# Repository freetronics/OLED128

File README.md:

Kicad Schematic and PCB layout files for the Freetronics OLED128 module. Based around the SSD1351 OLED controller chip.

Designed by Angus Gratton and Marc Alexander.

Copyright (C) 2013 Freetronics Pty Ltd. Open Source Hardware, licensed under the TAPR Open Hardware License.

# Resources

[OLED128 Home Page](http://freetronics.com/oled128)

[OLED128 QuickStart Guide](http://freetronics.com/pages/oled128-quickstart-guide)

[FTOLED Arduino Library](https://github.com/freetronics/FTOLED)

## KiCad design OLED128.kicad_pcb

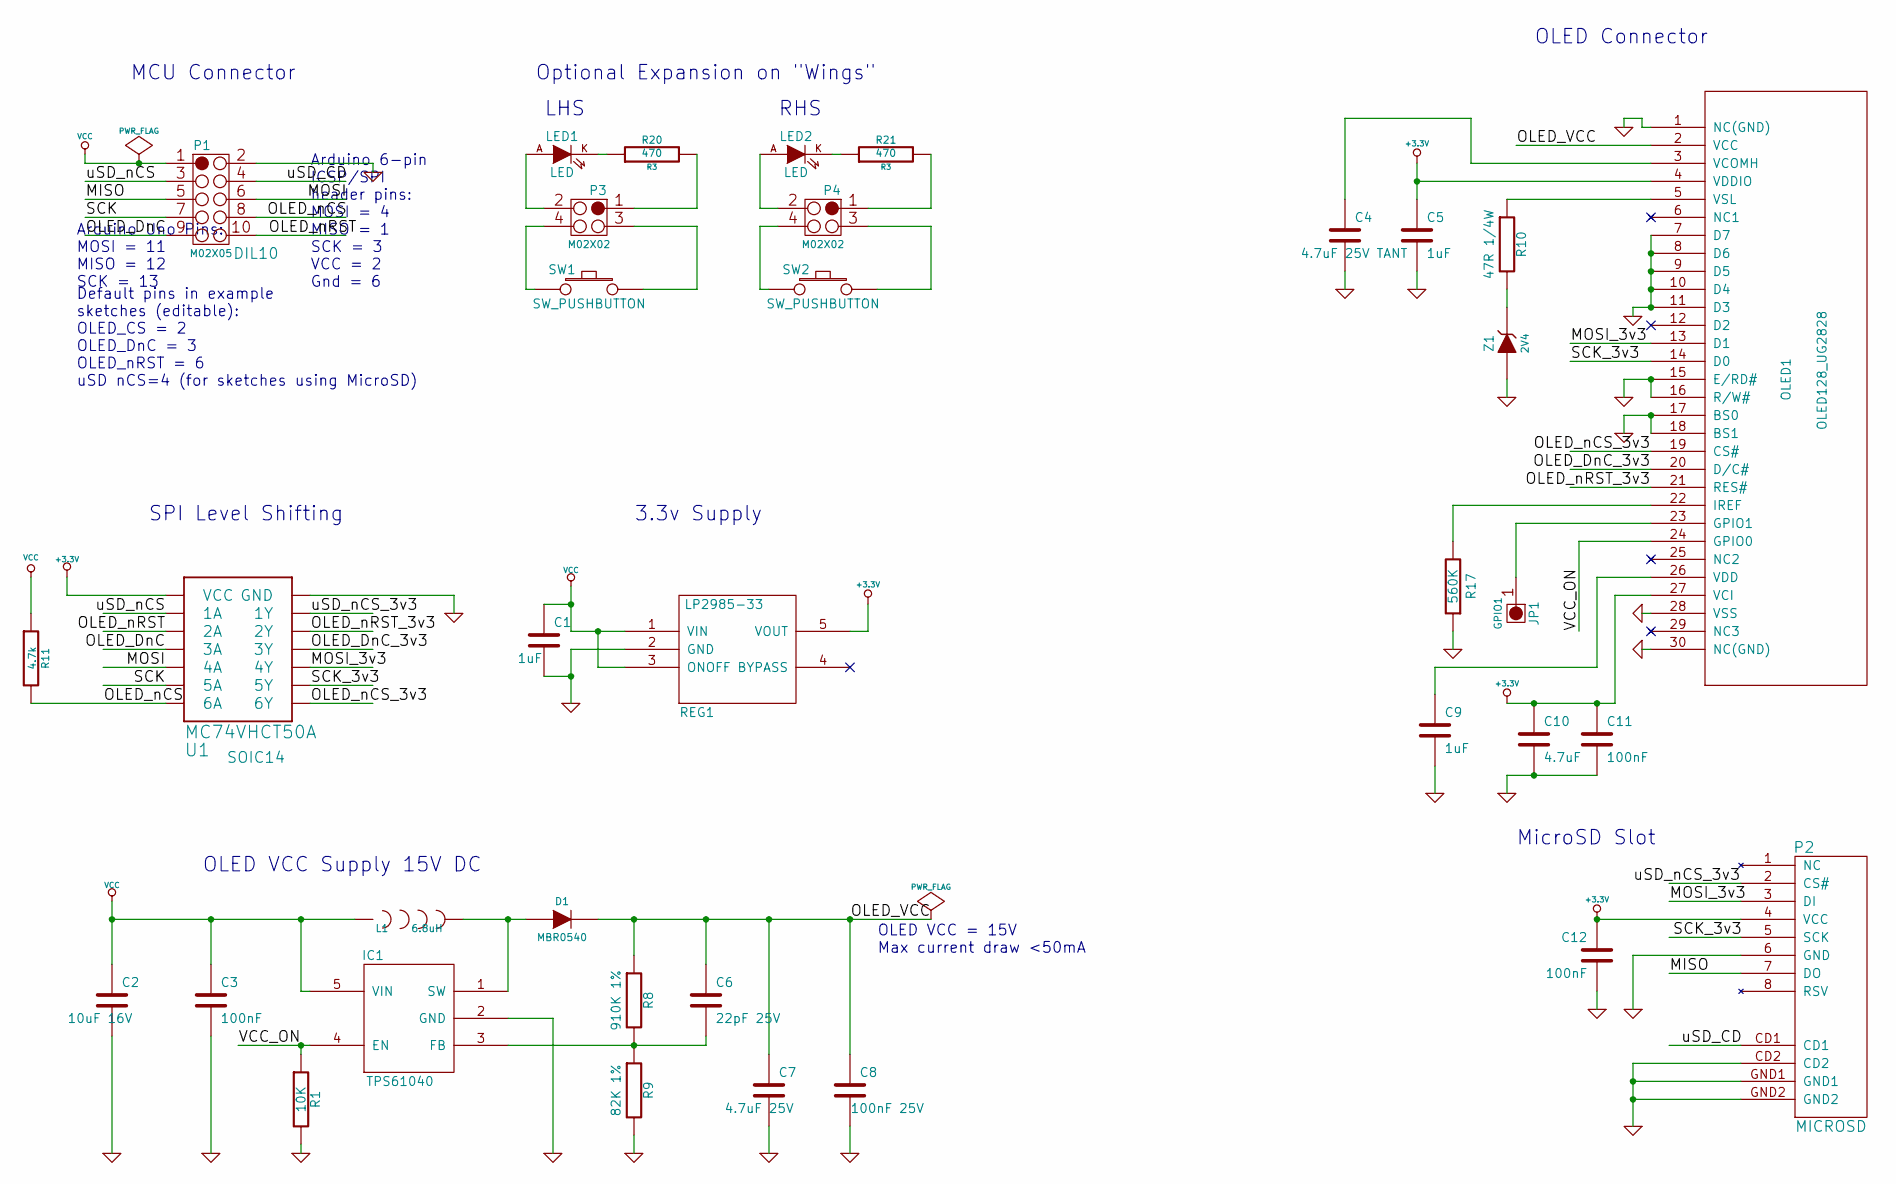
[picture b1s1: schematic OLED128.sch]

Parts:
C1, C5, C9: 1uF; 0603
C2: 10uF 16V; 0603
C3, C11, C12: 100nF; 0603
C4: 4.7uF 25V TANT; 1206
C6: 22pF 25V; 0603
C7: 4.7uF 25V; 0603
C8: 100nF 25V; 0603
C10: 4.7uF; 0603
D1: MBR0540; SOD-123
IC1: TPS61040; SOT23-5
JP1: GPIO1; 1X01
L1: 6.8uH; 1210
LED1, LED2: LED; LED3MM
OLED1: OLED128_UG2828; OLED-128X128-FPC-TOP
P1: M02X05; DIL10
P2: MICROSD; MICRO-SD-SOCKET-PP
P3, P4: M02X02; PIN_ARRAY_2X2
R1: 10K; 0603
R8: 910K 1%; 0603
R9: 82K 1%; 0603
R10: 47R 1/4W; 1206
R11: 4.7k
R17: 560K; 0603
R20, R21: 470; R3
REG1: LP2985-33; MODULE
SW1, SW2: SW_PUSHBUTTON; SW_TC0122
U1: MC74VHCT50A; SOIC14
Z1: 2V4; SOD-123

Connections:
+3.3V: C5.1, C10.1, C11.1, C12.1, OLED1.4 (VDDIO), OLED1.27 (VCI), P2.4 (VCC), REG1.5 (VOUT), U1.14 (VCC)
/MISO: P1.5, P2.7 (DO)
/MOSI: P1.6, U1.9 (4A)
/MOSI_3v3: OLED1.13 (D1), P2.3 (DI), U1.8 (4Y)
/OLED_DnC: P1.9, U1.5 (3A)
/OLED_DnC_3v3: OLED1.20 (D/C#), U1.6 (3Y)
/OLED_VCC: C6.1, C7.1, C8.1, D1.K, OLED1.2 (VCC), R8.1
/OLED_nCS: P1.8, R11.2, U1.13 (6A)
/OLED_nCS_3v3: OLED1.19 (CS#), U1.12 (6Y)
/OLED_nRST: P1.10, U1.3 (2A)
/OLED_nRST_3v3: OLED1.21 (RES#), U1.4 (2Y)
/SCK: P1.7, U1.11 (5A)
/SCK_3v3: OLED1.14 (D0), P2.5 (SCK), U1.10 (5Y)
/VCC_ON: IC1.4 (EN), OLED1.24 (GPIO0), R1.1
/uSD_CD: P1.4, P2.CD1
/uSD_nCS: P1.3, U1.1 (1A)
/uSD_nCS_3v3: P2.2 (CS#), U1.2 (1Y)
GND: C1.2, C2.2, C3.2, C4.2, C5.2, C7.2, C8.2, C9.2, C10.2, C11.2, C12.2, IC1.2 (GND), OLED1.1 (NC(GND)), OLED1.7 (D7), OLED1.8 (D6), OLED1.9 (D5), OLED1.10 (D4), OLED1.11 (D3), OLED1.15 (E/RD#), OLED1.16 (R/W#), OLED1.17 (BS0), OLED1.18 (BS1), OLED1.28 (VSS), OLED1.30 (NC(GND)), P1.2, P2.6 (GND), P2.CD2, P2.GND1, P2.GND2, R1.2, R9.2, R17.1, REG1.2 (GND), U1.7 (GND), Z1.A
unnamed: OLED1.22 (IREF), R17.2
unnamed: C4.1, OLED1.3 (VCOMH)
unnamed: D1.A, IC1.1 (SW), L1.2
unnamed: R10.2, Z1.K
unnamed: C6.2, IC1.3 (FB), R8.2, R9.1
unnamed: C9.1, OLED1.26 (VDD)
unnamed: OLED1.5 (VSL), R10.1
unnamed: P3.1, R20.2
unnamed: P3.4, SW1.1
unnamed: P3.3, SW1.2
unnamed: P4.3, SW2.2
unnamed: LED2.A, P4.2
unnamed: JP1.1, OLED1.23 (GPIO1)
unnamed: LED1.K, R20.1
unnamed: LED2.K, R21.1
unnamed: LED1.A, P3.2
unnamed: P4.4, SW2.1
unnamed: P4.1, R21.2
VCC: C1.1, C2.1, C3.1, IC1.5 (VIN), L1.1, P1.1, R11.1, REG1.1 (VIN), REG1.3 (ONOFF)

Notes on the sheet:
RHS
LHS
Optional Expansion on "Wings"
MicroSD Slot
SPI Level Shifting
MCU Connector
OLED Connector
OLED VCC Supply 15V DC
3.3v Supply
OLED VCC = 15V Max current draw <50mA
Arduino Uno Pins: MOSI = 11 MISO = 12 SCK = 13
Arduino 6-pin ICSP/SPI header pins: MOSI = 4 MISO = 1 SCK = 3 VCC = 2 Gnd = 6
Default pins in example sketches (editable): OLED_CS = 2 OLED_DnC = 3 OLED_nRST = 6 uSD nCS=4 (for sketches using MicroSD)

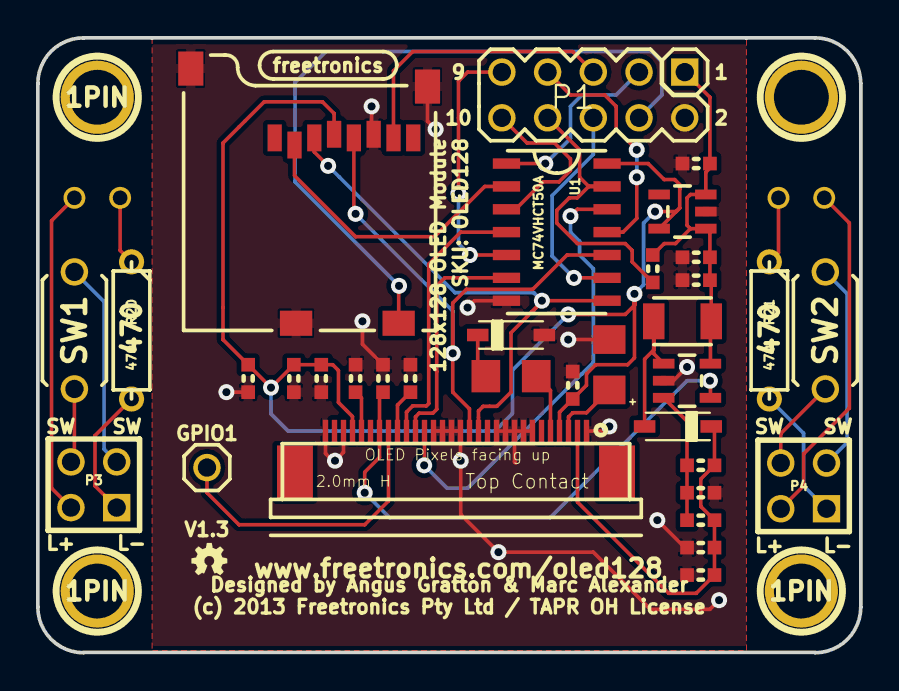
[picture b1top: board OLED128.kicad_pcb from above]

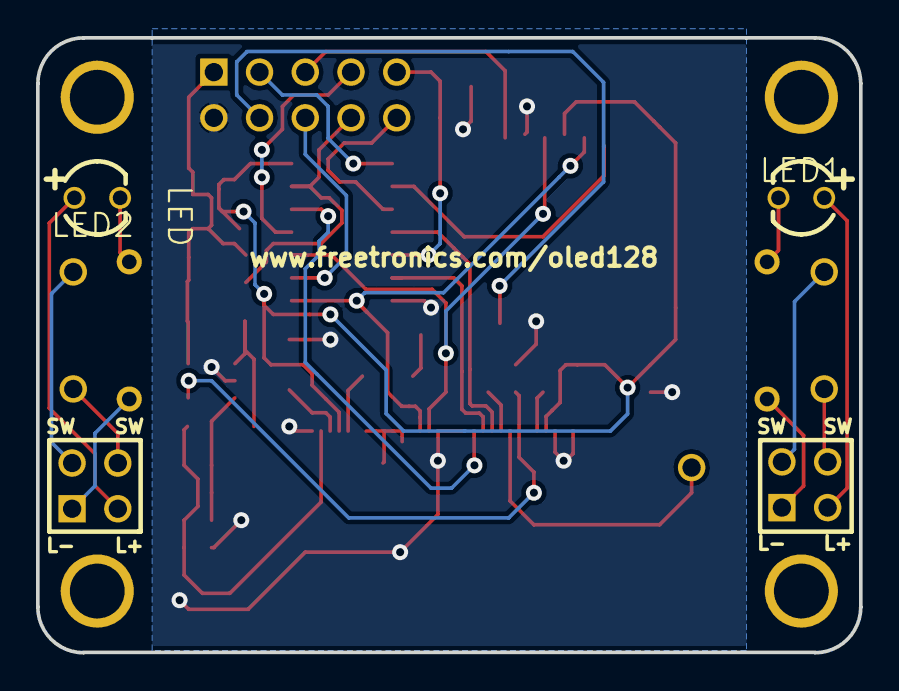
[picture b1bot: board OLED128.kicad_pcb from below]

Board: 2 copper layers, 45.7 x 34.2 mm, 41 parts (2 on the bottom side), 37 nets.

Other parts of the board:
1PIN, 1PIN#2, 1PIN#3, 1PIN#4: P***; 1pin
Ref**: Val**; LOGO_FREETRONICS_SMALL

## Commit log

2013-05-31 Initial commit, moved hardware components from FTOLED repo @ commit fe77584490bddff210091d671d63b1a6c4c6be1d
2013-05-31 Rename board components, update pcb file to use new s-expression format
2013-08-27 Add README, LICENSE
2013-08-27 Fix quickstart guide link
2014-11-10 Add dimensioned drawing

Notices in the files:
OLED128.kicad_pcb:
(c) 2013 Freetronics Pty Ltd / TAPR OH License
OLED128.sch:
Released under TAPR Open Hardware License www.tapr.org/ohl
